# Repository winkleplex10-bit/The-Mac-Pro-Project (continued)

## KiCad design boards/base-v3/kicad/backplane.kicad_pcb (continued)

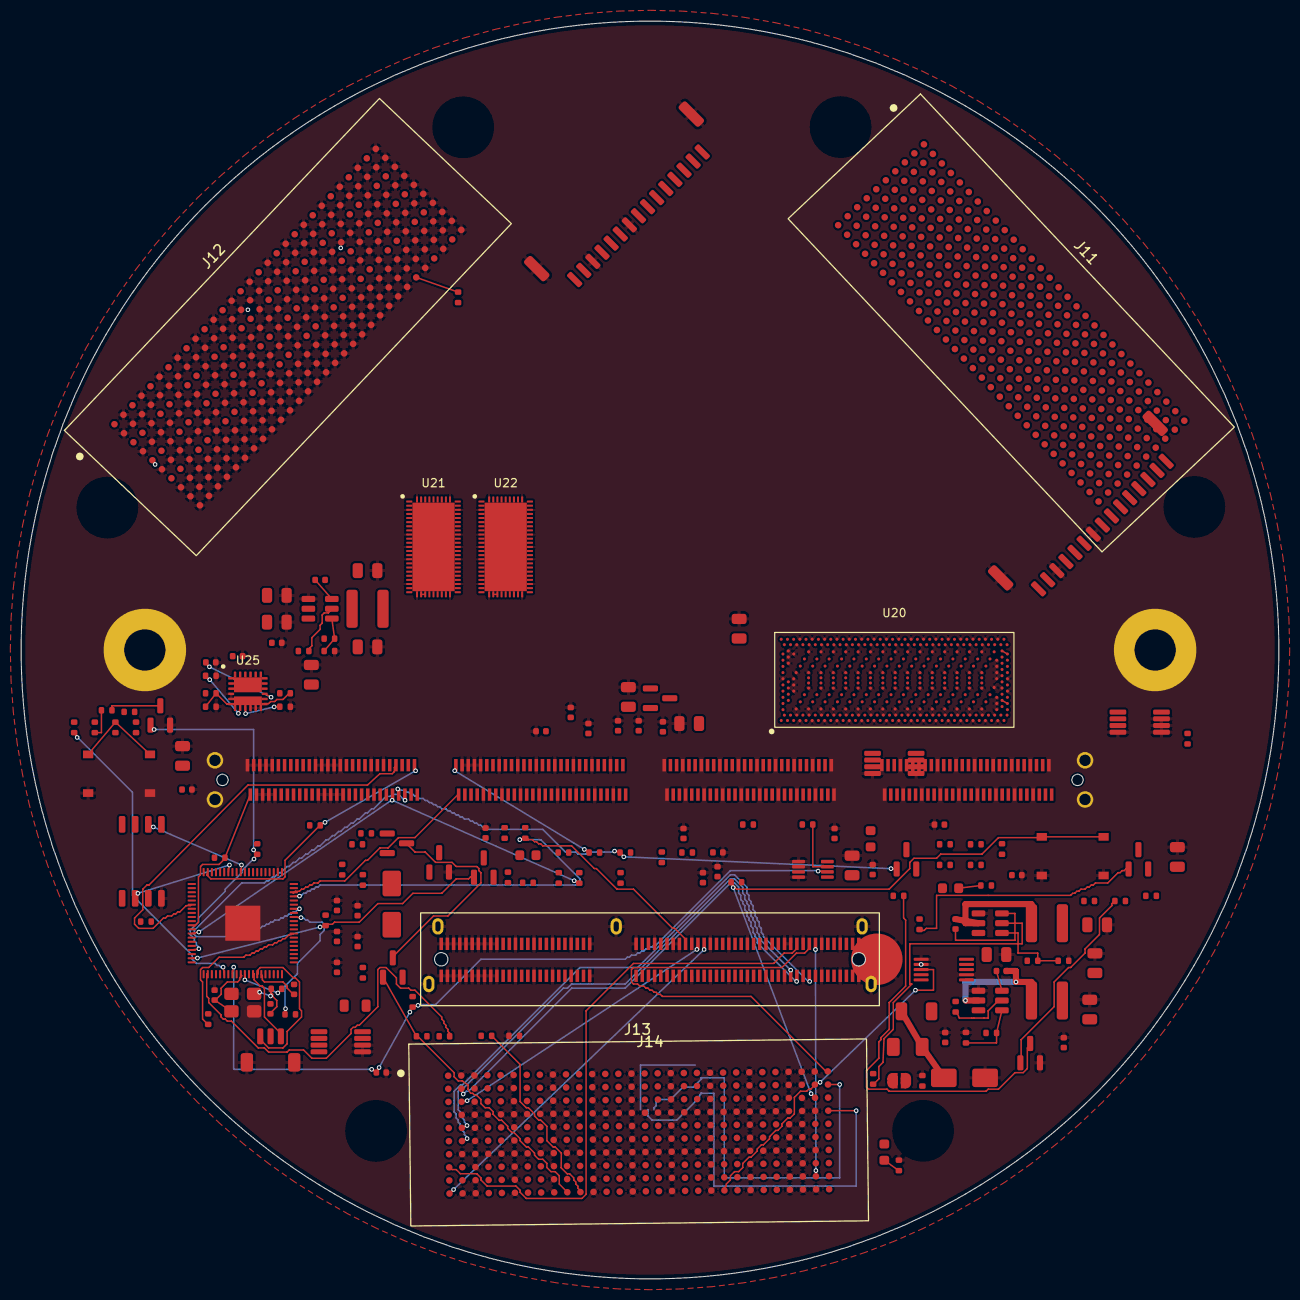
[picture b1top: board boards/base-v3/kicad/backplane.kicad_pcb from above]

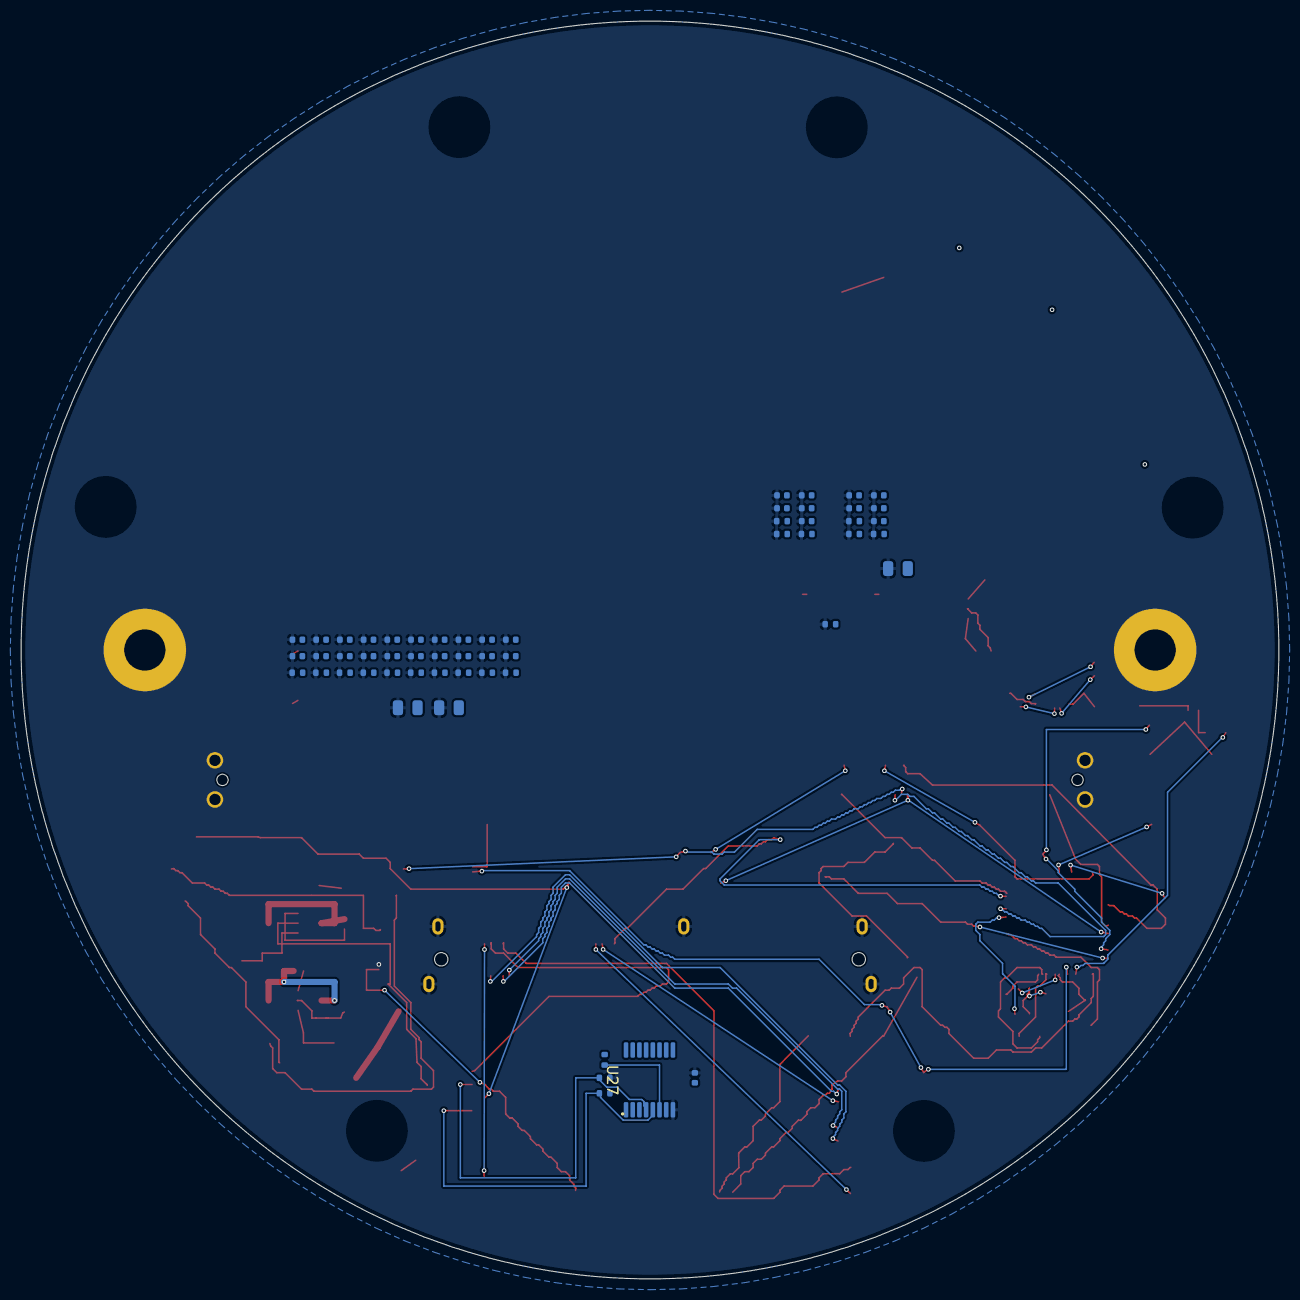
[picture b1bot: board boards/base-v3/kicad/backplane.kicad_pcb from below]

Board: 6 copper layers, 122.0 x 122.0 mm, 221 parts (55 on the bottom side), 327 nets.

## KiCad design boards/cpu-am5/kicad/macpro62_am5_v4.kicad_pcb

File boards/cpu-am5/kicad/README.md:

# MacPro6,2 AM5 CPU board (CB) - DRAFT rev A-am5, floorplan fp0 + block schematic bd0

> **2026-10-21 (Aidan approved):** CPU target = **Ryzen 7000/9000 (Raphael / Granite Ridge), GFX x16 → Face P**; Ryzen 8000G remains a **drop-in at x8** (Face P lanes 8-15 idle). Lane map: GFX x16 → Face P · GPP#1 x4 → Face S slot A · GPP#2 x4 → Face S slot B · x4 → PROM21 · **J8 M.2 boot on the PROM21 free Gen4 x4**. Power: stock 450 W PSU with firmware limits (PPT/TDC/EDC via the LPT; 45 W Eco as the fallback cap). BP v3 changes approved (INA226 swap, J7 DNP, storage-face deviations). Text below that says otherwise is history.

**Separate sibling project** of `kicad/macpro62-lga1700` (2026-10-04, Aidan). The LGA1700 project is **not modified**;
its generator logic and placements were read and reused. Plan: `/workspace/macpro62-am5-board-plan.md`
(sync zip: `docs/macpro62-am5-board-plan.md`). Spec: `macpro62-architecture-spec-v0.2.md` changelog item 35.
Cost basis: `macpro62-cost-estimate.md` §10.

Target (v3, approved 2026-10-21): **Ryzen 7000/9000 (Raphael / Granite Ridge), GFX x16 → Face P**, 65 W class with firmware power limits; **8000G = x8 drop-in**. v1 text kept below: ~~Ryzen 5 8600G / Ryzen 7 8700G (Phoenix) at cTDP 45 W~~ (Dasharo/openSIL boots only 8000G on AM5 today - open firmware item for 7000/9000);
Ryzen 7000/9000 = later option (lanes 8-15 to Face P already routed). **PROM21** chipset (218-0891025 preferred),
**SVI3 3-rail VRM** (5 VDDCR + 2 VDDCR_SOC + 1 VDD_MISC), **4 x DDR5 UDIMM vertical, 2DPC**.

Rebuild (KiCad 9, system python3 with pcbnew; needs ezdxf + shapely + PIL; reads
`/workspace/bracket/cpu_board/cpu_board_outline_corrected.dxf`):

    python3 tools/make_pinouts.py       # docs/*_am5.csv + pinout_delta_summary.txt (reads the lga1700 CSVs read-only)
    python3 tools/make_placeholders.py  # MP62_AM5_Placeholders.pretty + docs/u1_am5_lands_PLACEHOLDER.csv
    rm -f macpro62_am5_v4.kicad_pcb macpro62_am5_v4.kicad_pro macpro62_am5_v4.kicad_prl
    python3 tools/build_pcb.py          # writes fitcheck_floorplan.txt + placeholders_flagged.txt
    python3 tools/postprocess.py        # 10L stackup proposal + net classes
    kicad-cli pcb drc --severity-all -o drc_report.txt macpro62_am5_v4.kicad_pcb    # 0 violations
    sh tools/render.sh macpro62_am5_v4.kicad_pcb floorplan                          # floorplan.png / floorplan_notes.png
    python3 tools/build_sch.py          # block schematic (root + 10 stub sheets)
    kicad-cli sch erc --severity-all -o erc_report.txt macpro62_am5_v4.kicad_sch    # 0 violations
    kicad-cli sch export pdf -o schematic_blockdiagram.pdf macpro62_am5_v4.kicad_sch

Frame: x 0..156 right, y up from the board bottom (tab tip 1.722, shoulder 12.982, top 169.5); FRONT = socket/core side.
KiCad X = 60 + x, Y = 240 - y (identical to the LGA1700 CB).

## Reused unchanged from the LGA1700 CB (positions identical)
- Edge.Cuts (stock riser outline + Mini Cool Edge 224 tab), 1.6 mm, rules 0.09/0.09, via 0.25/0.15.
- H1-H4 core holes D5 at 69.5 x 55 (43.25/112.75, 46/101) + D12 boss keep-outs; H5-H8 frame seat screws (CX +-28, CY +-21).
- MP62 contact frame 71 x 54 + 4 ears (Eco1), steel backplate zone (B), pedestal (78.41, 73.25), black-plate 6.0 mm height zone.
- J1 CPU-LINK fingers, CAC1, J3 MCIO 124 RA (back, top), J8 M.2 2280 (back, bottom), 4 x DIMM (back, stock centrelines),
  LUG1/LUG2 + U11 eFuse + U15 INA228, GPU bus-bar pass-through keep-out, CB1/CB2, BT1 DNP, U14 DNP, EC/SPI/TPM/debug.

## New / changed for AM5
- **U1 Socket AM5 LGA1718 PLACEHOLDER**: 1718 SYNTHETIC lands on the sourced hex pitch 0.81 x 0.94 (Lotes brochure),
  package 40 x 40, housing 46 x 46 [Estimate], stock AM5 cooler 54 x 90 drawn on Dwgs only. **AMD land map = NDA -> do not fab.**
  Assumed land-group regions on Dwgs (DDR +y, PCIe -y) are [Inference].
- **U2 PROM21 PLACEHOLDER** FCBGA 19 x 19, 484 synthetic balls (ballout NDA), at the old PCH site (110, 133).
- VRM: 8 x SiC654 + 8 x FP4 (y 42-105), CIN1/COUT1 5 x 75, U3 SVI3 3-rail controller area (RAA229139 / MP2857) at (14, 117).
- Right column re-purposed: U4 CPU S5 rails, U5 sequencing/straps, U6 PROM21 rails, U7 5 V VIN_BULK, U8 VDDIO_MEM_S3.
- U16 VL822-Q7 USB 10G hub (90, 154), U17 PROM21 SPI (126, 150), Y1 48 MHz + 32 kHz.
- Pinouts: `docs/cpulink_224_pinout_am5.csv`, `docs/mp62-cb-j3_mcio124_host-end_am5.csv`, `docs/pinout_delta_summary.txt`
  (connector physicals + signal names unchanged -> BP / IOB need no change; delta vs ICD rev 3).

## Status
DRAFT floorplan: no nets, not routed. Every footprint carries an `MP62_STATUS` field; list in `placeholders_flagged.txt`
(PLACEHOLDER-NDA: U1, U2). Stackup is a proposal (placeholder dielectrics; take the JLC 10L table).

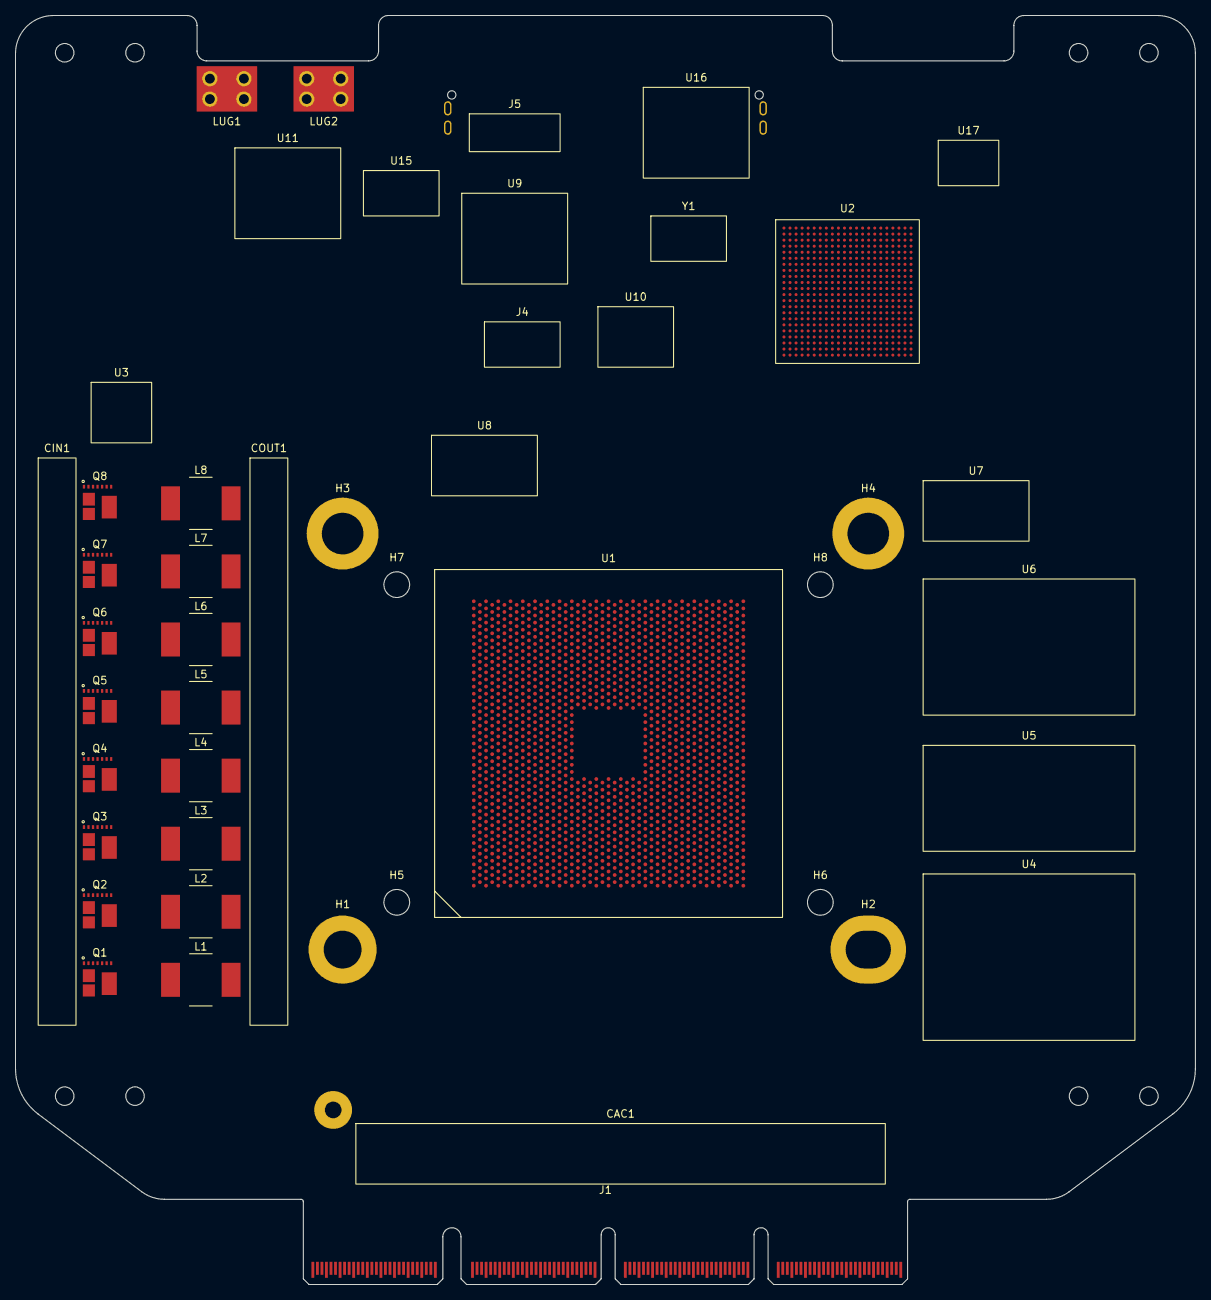
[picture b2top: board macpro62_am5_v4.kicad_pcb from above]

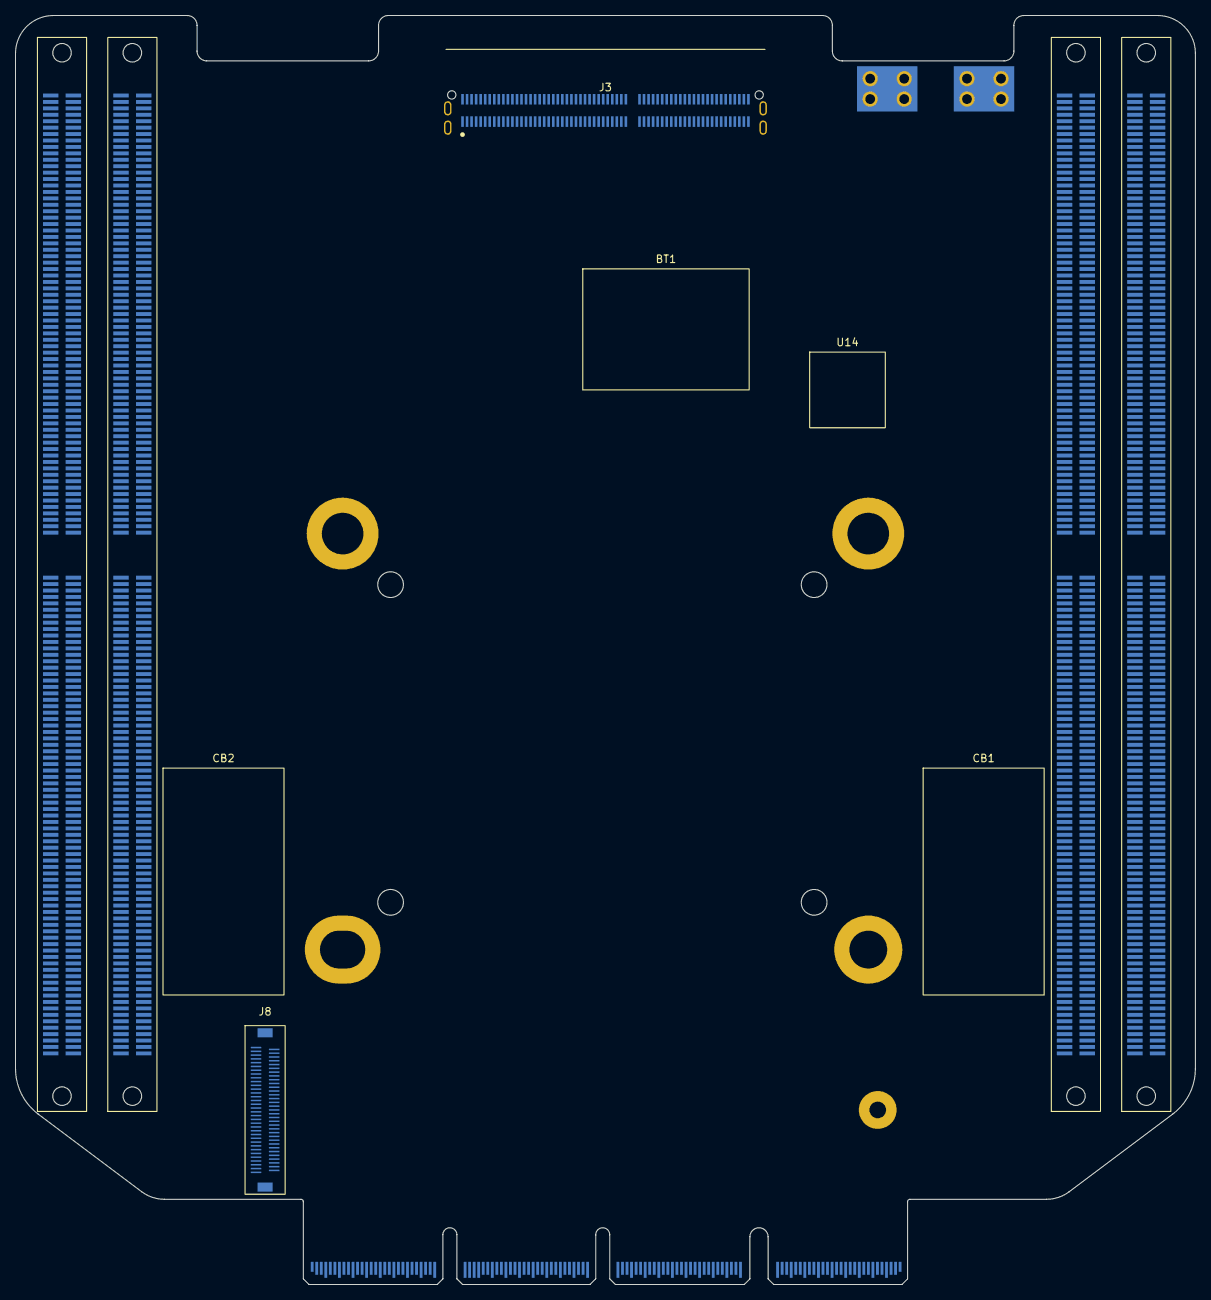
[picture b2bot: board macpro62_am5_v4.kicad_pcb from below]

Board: 10 copper layers, 156.0 x 167.8 mm, 57 parts (10 on the bottom side), 3 nets, no tracks yet.

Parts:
BT1: BT1 CR2032 DNP (VBAT_RTC from the IOB via J3 B26); MP62_AREA_BT1_CR2032_22x16
CAC1: PCIe AC caps (GFX x16 + GPP x4); MP62_AREA_PEG_ACcaps_70x8
CB1: 12V bulk L; MP62_AREA_Bulk12V_Back_16x30
CB2: 12V bulk R; MP62_AREA_Bulk12V_Back_16x30
CIN1: 12V in caps (8 phases); MP62_AREA_12V_InCaps_5x75
COUT1: VDDCR/SOC/MISC out caps; MP62_AREA_VDDCR_OutCaps_5x75
DIMM_A1: DIMM_A1 CH-A DIMM1 near DDR5 UDIMM; MP62_DIMM_DDR5_288P_Vert_UMAX_90414_ShortLatch
DIMM_A2: DIMM_A2 CH-A DIMM2 far DDR5 UDIMM; MP62_DIMM_DDR5_288P_Vert_UMAX_90414_ShortLatch
DIMM_B1: DIMM_B1 CH-B DIMM1 near DDR5 UDIMM; MP62_DIMM_DDR5_288P_Vert_UMAX_90414_ShortLatch
DIMM_B2: DIMM_B2 CH-B DIMM2 far DDR5 UDIMM; MP62_DIMM_DDR5_288P_Vert_UMAX_90414_ShortLatch
H1, H2, H3, H4: CORE D5 69.5x55 FIXED; MP62_CB_CoreMountHole_D5.0_Pad9
H5, H6, H7, H8: FRAME SEAT M3 -> PEM in backplate; MP62_CB_FrameSeatScrew_D3.4_NPTH
J1: J1 CPU-LINK 224 fingers (AM5 map: docs/cpulink_22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; MP62_CPULINK_MiniCoolEdge224_CardEdge_Fingers
J3: J3 IOB-HS MCIO 124 RA (AM5 host map docs/mp62-cb-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; MP62_MCIO_124P_RA_SFF-TA-1016
J4: J4 SPI TPM (opt.); MP62_AREA_TPM_Header_10x6
J5: J5 debug UART/SWD/POST; MP62_AREA_DebugHdr_12x5
J8: J8 M.2 2280 boot (PROM21 Gen4 x4, v3); MP62_CB_M2_2280_MKey_PLACEHOLDER
L1: L VDDCR 1 FP4-150-R; MP62_IND_Eaton_FP4_10.2x6.8x5.0
L2: L VDDCR 2 FP4-150-R; MP62_IND_Eaton_FP4_10.2x6.8x5.0
L3: L VDDCR 3 FP4-150-R; MP62_IND_Eaton_FP4_10.2x6.8x5.0
L4: L VDDCR 4 FP4-150-R; MP62_IND_Eaton_FP4_10.2x6.8x5.0
L5: L VDDCR 5 FP4-150-R; MP62_IND_Eaton_FP4_10.2x6.8x5.0
L6: L SOC 1 FP4-150-R; MP62_IND_Eaton_FP4_10.2x6.8x5.0
L7: L SOC 2 FP4-150-R; MP62_IND_Eaton_FP4_10.2x6.8x5.0
L8: L MISC FP4-150-R; MP62_IND_Eaton_FP4_10.2x6.8x5.0
LUG1: LUG1 GND?; MP62_CB_BusBarLug_8x6_PLACEHOLDER
LUG2: LUG2 12V?; MP62_CB_BusBarLug_8x6_PLACEHOLDER
Q1: PS VDDCR 1 SiC654; MP62_PowerStage_SiC654_MLP55-31L_5x5
Q2: PS VDDCR 2 SiC654; MP62_PowerStage_SiC654_MLP55-31L_5x5
Q3: PS VDDCR 3 SiC654; MP62_PowerStage_SiC654_MLP55-31L_5x5
Q4: PS VDDCR 4 SiC654; MP62_PowerStage_SiC654_MLP55-31L_5x5
Q5: PS VDDCR 5 SiC654; MP62_PowerStage_SiC654_MLP55-31L_5x5
Q6: PS SOC 1 SiC654; MP62_PowerStage_SiC654_MLP55-31L_5x5
Q7: PS SOC 2 SiC654; MP62_PowerStage_SiC654_MLP55-31L_5x5
Q8: PS MISC SiC654; MP62_PowerStage_SiC654_MLP55-31L_5x5
U1: U1 Socket AM5 LGA1718 PLACEHOLDER (PE17181 / AZIF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; MP62_AM5_LGA1718_Socket_PLACEHOLDER_Hex0.81x0.94
U2: U2 PROM21 218-0891025 PLACEHOLDER; MP62_PROM21_FCBGA_19x19_PLACEHOLDER
U3: U3 SVI3 3-rail ctrl RAA229139 (alt MP2857); MP62_AREA_SVI3_Ctrl_RAA229139_6x6
U4: CPU S5/aux rails (1.8/3.3/MISC_S5); MP62_AREA_CPU_S5_Rails_28x22
U5: CPU seq/straps/SVI3 pull-ups; MP62_AREA_CPU_Seq_Misc_28x14
U6: PROM21 rails; MP62_AREA_PROM21_Rails_28x18
U7: 5V VIN_BULK 4x UDIMM; MP62_AREA_5V_DIMM_VINBULK_14x8
U8: VDDIO_MEM_S3 1.1V; MP62_AREA_VDDIO_MEM_Buck_14x8
U9: U9 EC RP2350; MP62_AREA_EC_RP2350_14x12
U10: U10 FCH SPI 32MB (Dasharo); MP62_AREA_BIOS_SPI_W25Q256_10x8
U11: U11 eFuse 12V IN (whole CB); MP62_AREA_eFuse_TPS25985_14x12
U14: U14 ALC897 DNP (FCH AZ); MP62_AREA_HDA_ALC897_DNP_10x10
U15: U15 INA228 + RS1 0.5 mOhm (12V in, I2C0 0x45); MP62_AREA_PwrMon_INA228_10x6
U16: U16 VL822-Q7 USB 10G hub (J3 A1-A4); MP62_AREA_USB10G_Hub_VL822_14x12
U17: U17 PROM21 SPI flash; MP62_AREA_PROM21_SPI_8x6
Y1: Y1/Y2 48M + 32k (FCH); MP62_AREA_CLK_XTAL_10x6

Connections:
3V3_SB: J1.B107, J1.B108
5V_SBY: J1.A107, J1.A108, J1.A110, J1.A111, J1.B110, J1.B111
GND: J1.A4, J1.A7, J1.A10, J1.A13, J1.A16, J1.A19, J1.A22, J1.A25, J1.A28, J1.A29, J1.A32, J1.A35, J1.A38, J1.A41, J1.A44, J1.A47, J1.A50, J1.A53, J1.A56, J1.A57, J1.A60, J1.A63, J1.A66, J1.A69, J1.A72, J1.A75, J1.A78, J1.A81, J1.A84, J1.A85, J1.A88, J1.A91, J1.A94, J1.A97, J1.A100, J1.A103, J1.A106, J1.A109, J1.B1, J1.B4, J1.B7, J1.B10, J1.B13, J1.B16, J1.B19, J1.B22, J1.B25, J1.B28, J1.B29, J1.B32, J1.B35, J1.B38, J1.B41, J1.B44, J1.B47, J1.B50, J1.B53, J1.B56, J1.B57, J1.B60, J1.B63, J1.B66, J1.B69, J1.B72, J1.B75, J1.B78, J1.B81, J1.B84, J1.B85, J1.B88, J1.B91, J1.B94, J1.B97, J1.B100, J1.B103, J1.B106, J1.B109, J1.B112, J3.A1, J3.A4, J3.A7, J3.A10, J3.A13, J3.A16, J3.A19, J3.A22, J3.A25, J3.A28, J3.A31, J3.A34, J3.A37, J3.A38, J3.A41, J3.A44, J3.A47, J3.A50, J3.A53, J3.A56, J3.A59, J3.A62, J3.B1, J3.B4, J3.B7, J3.B10, J3.B13, J3.B16, J3.B19, J3.B22, J3.B25, J3.B28, J3.B31, J3.B34, J3.B37, J3.B38, J3.B41, J3.B44, J3.B47, J3.B50, J3.B53, J3.B56, J3.B59, J3.B62, J3.MP

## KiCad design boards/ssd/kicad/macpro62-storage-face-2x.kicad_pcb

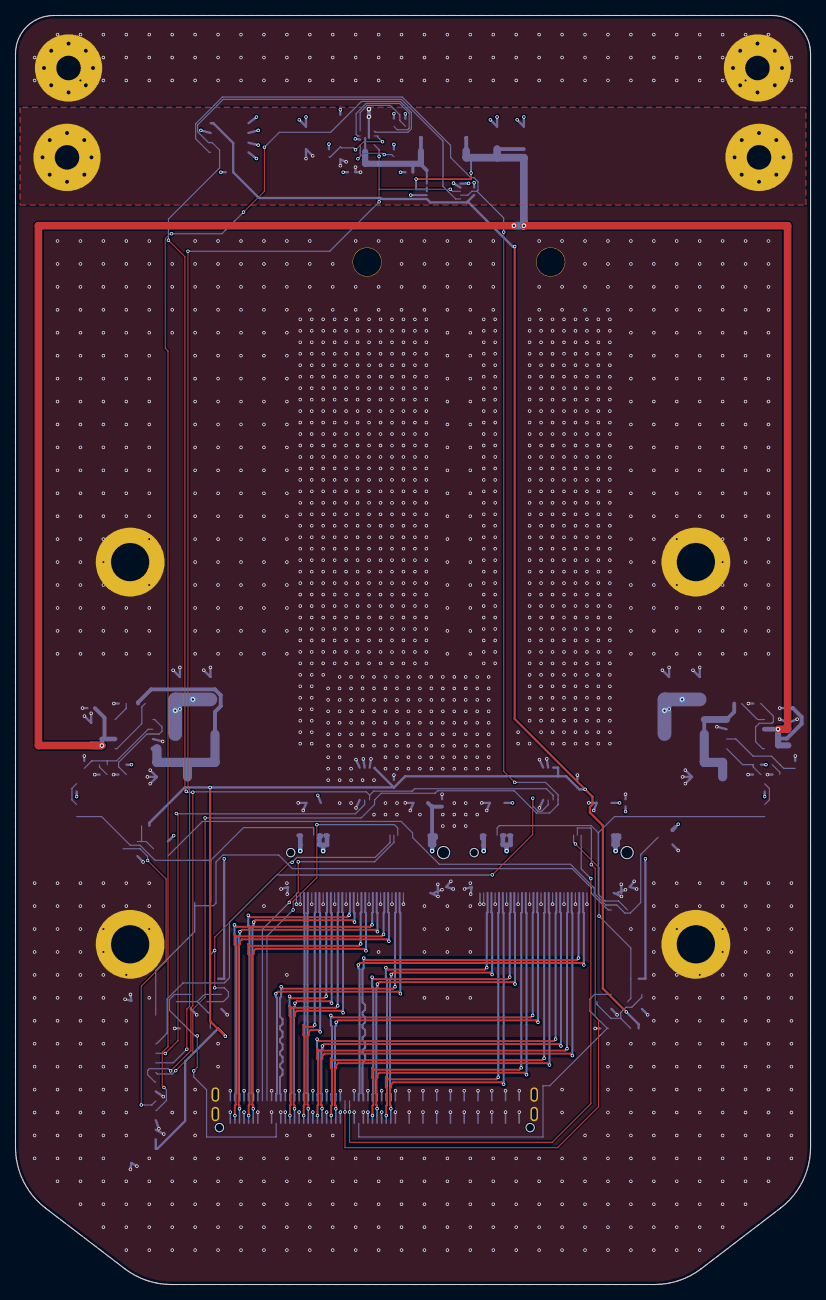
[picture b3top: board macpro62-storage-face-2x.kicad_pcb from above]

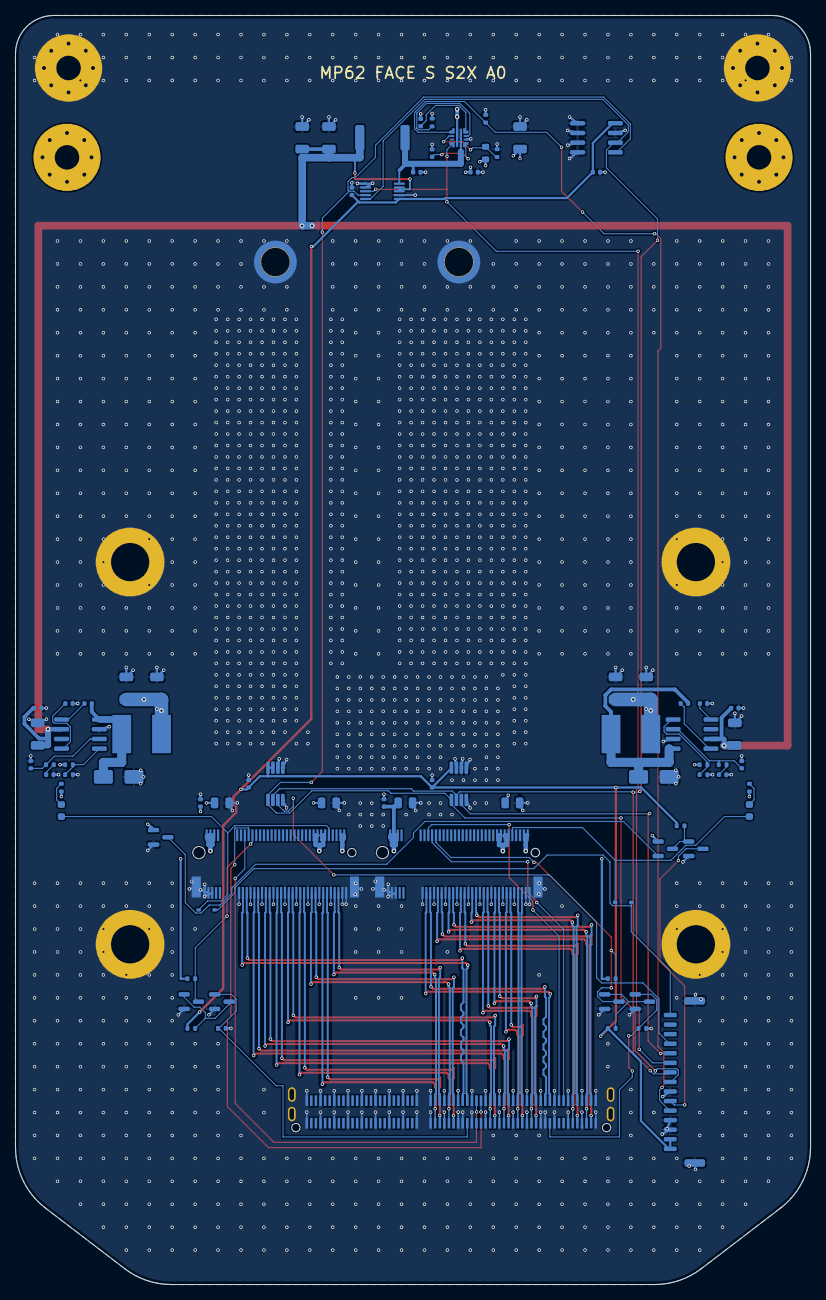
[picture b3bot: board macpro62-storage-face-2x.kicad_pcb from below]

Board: 4 copper layers, 104.0 x 166.0 mm, 89 parts (81 on the bottom side), 83 nets.

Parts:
C1: 3.3nF 50V; C_0402_1005Metric
C2: 2.2nF 50V; C_0402_1005Metric
C3, C7, C8: 22uF 25V X5R; C_1206_3216Metric
C4, C5, C10, C11, C18, C19: 100nF 50V; C_0402_1005Metric
C6, C27, C30, C31, C32, C33: 100nF 16V; C_0402_1005Metric
C9, C17: 10uF 50V X5R; C_1206_3216Metric
C12, C20: 10nF 50V; C_0402_1005Metric
C13, C21: 1nF 50V; C_0402_1005Metric
C14, C22: 47pF 50V; C_0402_1005Metric
C15, C16, C23, C24: 47uF 10V X5R; C_1206_3216Metric
C25, C26, C28, C29: 22uF 25V X5R; C_0805_2012Metric
D1, D2: SS34; D_SMA
D3, D4: red 0603; LED_0603_1608Metric
D5, D6: RB751V-40; D_SOD-323
H1, H2, H3, H4: MOUNT D5.0; MP62_FACE_MountHole_D5.0_Pad9.0
J1: MCIO 124P RA G97R24332HR (J_PCIE, lanes 0-7: x4 s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; MP62_MCIO_124P_RA_SFF-TA-1016
J3: SM15B-GHS-TB GH15 RA (J_AUX); JST_GH_SM15B-GHS-TB_1x15-1MP_P1.25mm_Horizontal
J5: M.2 M-key slot A (LOTES APCI0107-P001A); M2_M-Key_LOTES_APCI0107-P001A
J6: M.2 M-key slot B (LOTES APCI0107-P001A); M2_M-Key_LOTES_APCI0107-P001A
J20: BUSBAR LUG site A +12V_IN; MP62_FACE_BusBarLug_D3.2_Pad8.8
J21: BUSBAR LUG site A GND; MP62_FACE_BusBarLug_D3.2_Pad8.8
J22: BUSBAR LUG site B +12V_IN; MP62_FACE_BusBarLug_D3.2_Pad8.8
J23: BUSBAR LUG site B GND; MP62_FACE_BusBarLug_D3.2_Pad8.8
L1, L2: 6.8uH 4.3A SWPA6045S6R8MT; L_Sunlord_SWPA6045S
MH1, MH2: SMTSO2030CTJ M2 standoff (2280); M2_Standoff_SMTSO2030CTJ_M2_H3.0
Q1, Q2, Q3, Q4, Q5, Q6, Q7: 2N7002; SOT-23
R1, R12, R15, R20: 100k; R_0402_1005Metric
R2: 120k 1%; R_0603_1608Metric
R3: 10k 1%; R_0402_1005Metric
R4, R18, R19: 1k; R_0402_1005Metric
R5: 2mR 1% 2W; R_2512_6332Metric
R6, R9: 4.7k 1%; R_0402_1005Metric
R7, R10: 1.5k 1%; R_0402_1005Metric
R8, R11: 27k; R_0402_1005Metric
R13, R14, R16, R17: 10k; R_0402_1005Metric
U1: TPS259470ARPWR; TI_RPW_VQFN-10_2x2mm_P0.45mm
U2: INA238AIDGSR @0x40; VSSOP-10_3x3mm_P0.5mm
U3, U4: TPS54331DR; SOIC-8_3.9x4.9mm_P1.27mm
U6: TMP1075DGKR @0x48 (THERM_ALERT#); VSSOP-8_3x3mm_P0.65mm
U7: TMP1075DGKR @0x49 (THERM_TRIP#, 80 C POR default); VSSOP-8_3x3mm_P0.65mm
U8: M24C64-RMN6TP @0x50 (FRU / ID); SOIC-8_3.9x4.9mm_P1.27mm

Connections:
3V3_A: C15.1, C16.1, C25.1, C26.1, C27.1, J5.2, J5.4, J5.12, J5.14, J5.16, J5.18, J5.70, J5.72, J5.74, L1.2, Q6.1, R6.1, R14.1, R18.1
3V3_AUX: C6.1, C31.1, C32.1, C33.1, J3.1, J3.2, R13.1, R16.1, R20.1, U2.6, U6.8, U7.7, U7.8, U8.8
3V3_B: C23.1, C24.1, C28.1, C29.1, C30.1, J6.2, J6.4, J6.12, J6.14, J6.16, J6.18, J6.70, J6.72, J6.74, L2.2, Q7.1, R9.1, R17.1, R19.1
+12V_IN: C3.1, C4.1, J20.1, J22.1, R2.1, U1.5
+12V_S: C7.1, C8.1, C9.1, C10.1, C17.1, C18.1, R5.2, U2.8, U2.9, U3.2, U4.2
+12V_SW: C5.1, R5.1, U1.6, U2.10
BOOT_A: C11.1, U3.1
BOOT_B: C19.1, U4.1
CLKREQ_A_N: J1.B8, J5.52
CLKREQ_B_N: J1.B26, J6.52
COMP_A: C14.1, R8.1, U3.6
COMP_B: C22.1, R11.1, U4.6
CRC_A: C13.1, R8.2
CRC_B: C21.1, R11.2
DAS_A_N: D3.1, D5.1, J5.10
DAS_B_N: D4.1, D6.1, J6.10
EF_DVDT: C1.1, U1.7
EF_ILM: R4.1, U1.9
EF_ITIMER: C2.1, U1.10
EF_OVLO: R2.2, R3.1, U1.2
FACE_PWR_EN: J3.5, R1.1, U1.1
FACE_PWR_GOOD: J3.6, Q5.3
FACE_SMB_ALERT_N: J3.10, U1.4, U2.3
FACE_SMB_CLK: J3.8, U2.5, U6.2, U7.2, U8.6
FACE_SMB_DAT: J3.9, U2.4, U6.1, U7.1, U8.5
FB_A: R6.2, R7.1, U3.5
FB_B: R9.2, R10.1, U4.5
GND: C1.2, C2.2, C3.2, C4.2, C5.2, C6.2, C7.2, C8.2, C9.2, C10.2, C12.2, C13.2, C14.2, C15.2, C16.2, C17.2, C18.2, C20.2, C21.2, C22.2, C23.2, C24.2, C25.2, C26.2, C27.2, C28.2, C29.2, C30.2, C31.2, C32.2, C33.2, D1.2, D2.2, H1.1, H2.1, H3.1, H4.1, J1.A1, J1.A4, J1.A7, J1.A10, J1.A12, J1.A13, J1.A16, J1.A19, J1.A22, J1.A25, J1.A28, J1.A30, J1.A31, J1.A34, J1.A37, J1.A38, J1.A41, J1.A44, J1.A47, J1.A50, J1.A53, J1.A56, J1.A59, J1.A62, J1.B1, J1.B4, J1.B7, J1.B10, J1.B13, J1.B16, J1.B19, J1.B22, J1.B25, J1.B28, J1.B31, J1.B34, J1.B37, J1.B38, J1.B41, J1.B44, J1.B47, J1.B50, J1.B53, J1.B56, J1.B59, J1.B62, J1.MP, J3.3, J3.4, J3.7, J3.MP, J5.1, J5.3, J5.9, J5.15, J5.21, J5.27, J5.33, J5.39, J5.45, J5.51, J5.57, J5.71, J5.73, J5.75, J5.76, J5.77, J6.1, J6.3, J6.9, J6.15, J6.21, J6.27, J6.33, J6.39, J6.45, J6.51, J6.57, J6.71, J6.73, J6.75, J6.76, J6.77, J21.1, J23.1, MH1.1, MH2.1, Q1.2, Q2.2, Q3.2, Q4.2, Q5.2, Q7.2, R1.2, R3.2, R4.2, R7.2, R10.2, R12.2, R15.2, U1.8, U2.1, U2.2, U2.7, U3.7, U4.7, U6.4, U6.5, U6.6, U6.7, U7.4, U7.5, U7.6, U8.1, U8.2, U8.3, U8.4, U8.7
LED_A_A: D3.2, R18.2
LED_B_A: D4.2, R19.2
MOD_LED_N: D5.2, D6.2, J3.15
PCIE_A_HTX0_N: J1.A3, J5.49
PCIE_A_HTX0_P: J1.A2, J5.47
PCIE_A_HTX1_N: J1.A6, J5.37
PCIE_A_HTX1_P: J1.A5, J5.35
PCIE_A_HTX2_N: J1.A15, J5.25
PCIE_A_HTX2_P: J1.A14, J5.23
PCIE_A_HTX3_N: J1.A18, J5.13
PCIE_A_HTX3_P: J1.A17, J5.11
PCIE_A_MTX0_N: J1.B3, J5.43
PCIE_A_MTX0_P: J1.B2, J5.41
PCIE_A_MTX1_N: J1.B6, J5.31
PCIE_A_MTX1_P: J1.B5, J5.29
PCIE_A_MTX2_N: J1.B15, J5.19
PCIE_A_MTX2_P: J1.B14, J5.17
PCIE_A_MTX3_N: J1.B18, J5.7
PCIE_A_MTX3_P: J1.B17, J5.5
PCIE_B_HTX0_N: J1.A21, J6.49
PCIE_B_HTX0_P: J1.A20, J6.47
PCIE_B_HTX1_N: J1.A24, J6.37
PCIE_B_HTX1_P: J1.A23, J6.35
PCIE_B_HTX2_N: J1.A33, J6.25
PCIE_B_HTX2_P: J1.A32, J6.23
PCIE_B_HTX3_N: J1.A36, J6.13
PCIE_B_HTX3_P: J1.A35, J6.11
PCIE_B_MTX0_N: J1.B21, J6.43
PCIE_B_MTX0_P: J1.B20, J6.41
PCIE_B_MTX1_N: J1.B24, J6.31
PCIE_B_MTX1_P: J1.B23, J6.29
PCIE_B_MTX2_N: J1.B33, J6.19
PCIE_B_MTX2_P: J1.B32, J6.17
PCIE_B_MTX3_N: J1.B36, J6.7
PCIE_B_MTX3_P: J1.B35, J6.5
PERST_A_HOST_N: J1.A11, Q1.1, R12.1
PERST_A_INV: Q1.3, Q2.1, R13.2
PERST_A_N: J5.50, Q2.3, R14.2
PERST_B_HOST_N: J1.A29, Q3.1, R15.1
PERST_B_INV: Q3.3, Q4.1, R16.2
PERST_B_N: J6.50, Q4.3, R17.2
PG_G: Q5.1, Q6.3, R20.2
PG_M: Q6.2, Q7.3
PH_A: C11.2, D1.1, L1.1, U3.8
PH_B: C19.2, D2.1, L2.1, U4.8
REFCLK_A_N: J1.B12, J5.53
REFCLK_A_P: J1.B11, J5.55
REFCLK_B_N: J1.B30, J6.53
REFCLK_B_P: J1.B29, J6.55
SS_A: C12.1, U3.4
SS_B: C20.1, U4.4
THERM_ALERT_N: J3.11, U6.3
THERM_TRIP_N: J3.12, U7.3
WAKE_A_N: J1.B9, J5.54
WAKE_B_N: J1.B27, J6.54
